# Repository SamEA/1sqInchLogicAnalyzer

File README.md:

1sqInchLogicAnalyzer
====================

The smallest Logic Analyzer. It is powered with the common  CY7C68013A and it is compatible with  the most Open Source Software(

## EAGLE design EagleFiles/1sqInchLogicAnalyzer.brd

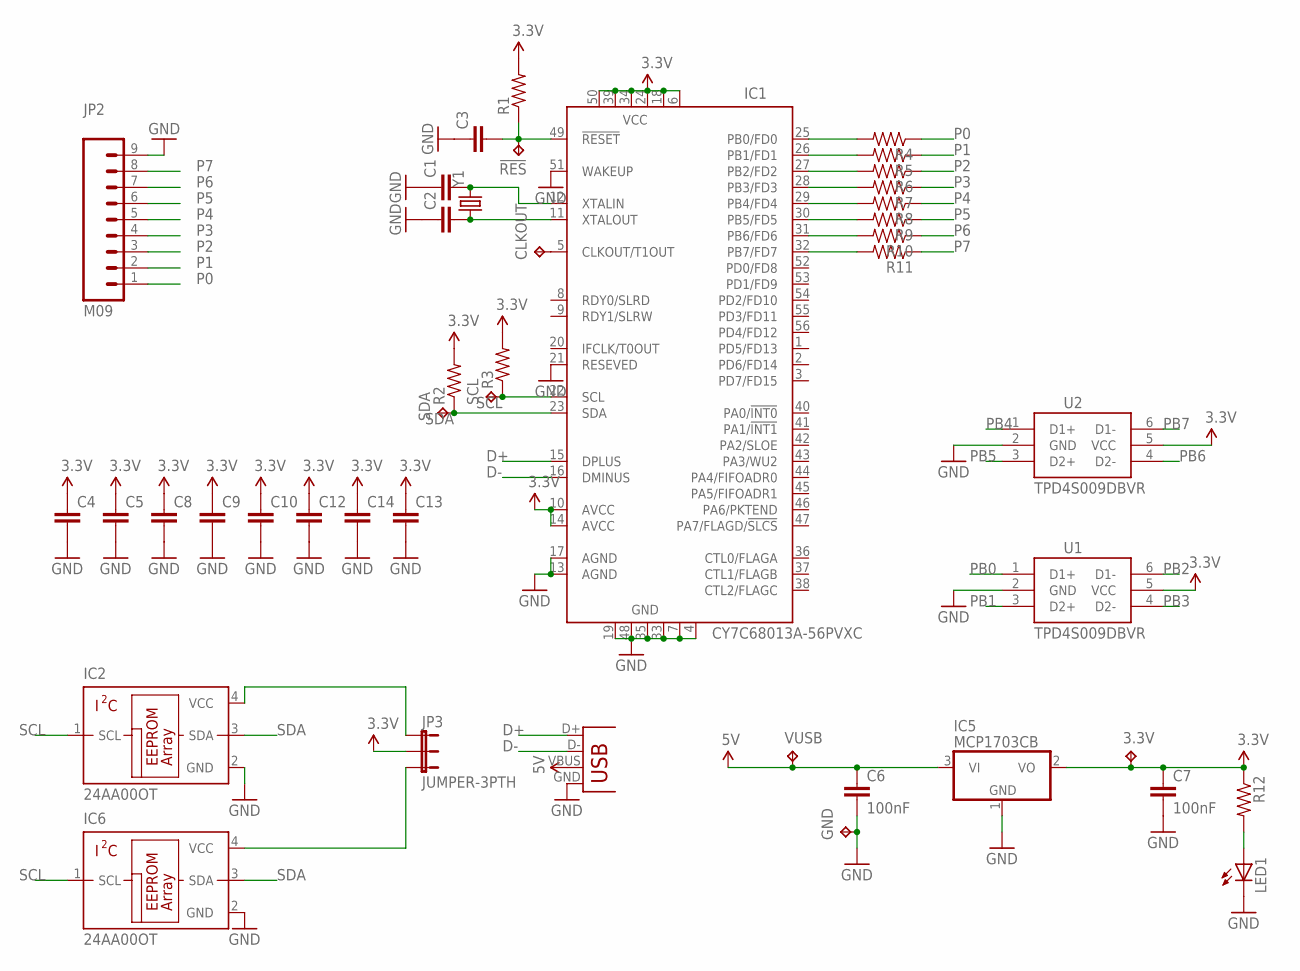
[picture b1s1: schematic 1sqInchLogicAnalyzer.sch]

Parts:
3.3V: TPTP07R; TP07R
!RES: TPTP07R; TP07R
C1, C2, C3, C4, C5, C8, C9, C10, C12, C13, C14: CAP0402-CAP; 0402-CAP
C6, C7: 100nF; 0603-CAP
CLKOUT: TPTP07R; TP07R
GND: TPTP07R; TP07R
IC1: CY7C68013A-56PVXC; SSOP56
IC2, IC6: 24AA00OT; SOT23-5L
IC5: MCP1703CB; SOT23
JP2: M09; 1X09
JP3: JUMPER-3PTH; 1X03
LED1: LED0603; LED-0603
R1, R2, R3, R4, R5, R6, R7, R8, R9, R10, R11, R12: RESISTOR0402-RES; 0402-RES
SCL: TPTP07R; TP07R
SDA: TPTP07R; TP07R
U1, U2: TPD4S009DBVR
VUSB: TPTP07R; TP07R
X2: USB-MICROB
Y1: CRYSTAL5X3; CRYSTAL-SMD-5X3

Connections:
3.3V: 3.3V.TP, C4.1, C5.1, C7.1, C8.1, C9.1, C10.1, C12.1, C13.1, C14.1, IC1.6 (VCC), IC1.10 (AVCC), IC1.14 (AVCC), IC1.18 (VCC), IC1.24 (VCC), IC1.34 (VCC), IC1.39 (VCC), IC1.50 (VCC), IC5.2 (VO), JP3.2, R1.2, R2.2, R3.2, R12.1, U1.5 (VCC), U2.5 (VCC)
5V: C6.1, IC5.3 (VI), VUSB.TP, X2.VBUS
D+: IC1.15 (DPLUS), X2.D+
D-: IC1.16 (DMINUS), X2.D-
GND: C1.1, C2.1, C3.1, C4.2, C5.2, C6.2, C7.2, C8.2, C9.2, C10.2, C12.2, C13.2, C14.2, GND.TP, IC1.4 (GND), IC1.7 (GND), IC1.13 (AGND), IC1.17 (AGND), IC1.19 (GND), IC1.21 (RESEVED), IC1.33 (GND), IC1.35 (GND), IC1.48 (GND), IC1.51 (WAKEUP), IC2.2 (GND), IC5.1 (GND), IC6.2 (GND), JP2.9, LED1.C, U1.2 (GND), U2.2 (GND), X2.GND
unnamed: IC6.4 (VCC), JP3.3
unnamed: IC2.4 (VCC), JP3.1
unnamed: C1.2, IC1.12 (XTALIN), Y1.3 (2)
unnamed: C2.2, IC1.11 (XTALOUT), Y1.1
unnamed: !RES.TP, C3.2, IC1.49 (!RESET), R1.1
unnamed: LED1.A, R12.2
unnamed: CLKOUT.TP, IC1.5 (CLKOUT/T1OUT)
P0: JP2.1, R4.1
P1: JP2.2, R5.1
P2: JP2.3, R6.1
P3: JP2.4, R7.1
P4: JP2.5, R8.1
P5: JP2.6, R9.1
P6: JP2.7, R10.1
P7: JP2.8, R11.1
PB0: IC1.25 (PB0/FD0), R4.2, U1.1 (D1+)
PB1: IC1.26 (PB1/FD1), R5.2, U1.3 (D2+)
PB2: IC1.27 (PB2/FD2), R6.2, U1.6 (D1-)
PB3: IC1.28 (PB3/FD3), R7.2, U1.4 (D2-)
PB4: IC1.29 (PB4/FD4), R8.2, U2.1 (D1+)
PB5: IC1.30 (PB5/FD5), R9.2, U2.3 (D2+)
PB6: IC1.31 (PB6/FD6), R10.2, U2.4 (D2-)
PB7: IC1.32 (PB7/FD7), R11.2, U2.6 (D1-)
SCL: IC1.22 (SCL), IC2.1 (SCL), IC6.1 (SCL), R3.1, SCL.TP
SDA: IC1.23 (SDA), IC2.3 (SDA), IC6.3 (SDA), R2.1, SDA.TP

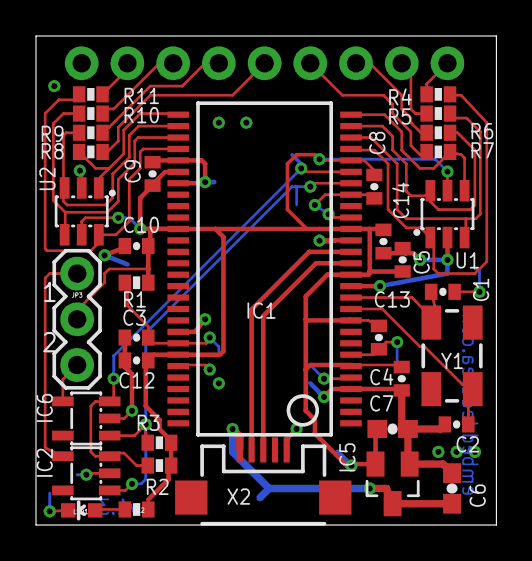
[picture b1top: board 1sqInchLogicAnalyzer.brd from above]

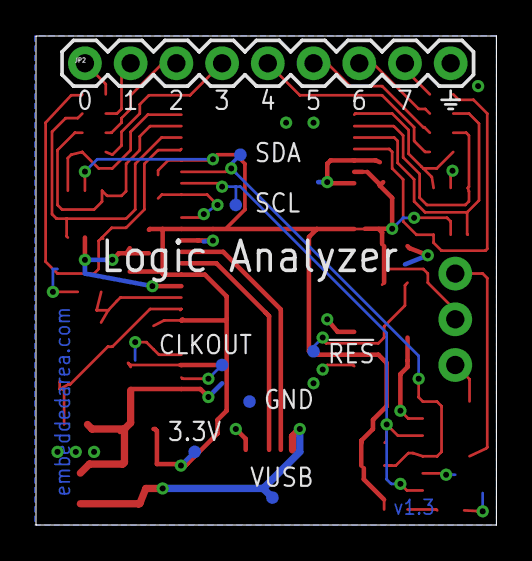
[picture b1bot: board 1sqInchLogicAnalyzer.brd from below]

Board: 2 copper layers, 25.6 x 27.2 mm, 43 parts (8 on the bottom side), 30 nets.

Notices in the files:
parts and their libraries:
SparkFun-Connectors: Licensing: CC v3.0 Share-Alike You are welcome to use this library for commercial purposes.
